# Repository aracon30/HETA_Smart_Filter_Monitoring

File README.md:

# HETA Smart Filter Monitoring &nbsp;

Industrielles Filterüberwachungssystem für den **Raspberry Pi** (3B+ / 4 / 5). Erfasst 4–20-mA-Sensordaten
via AnoPi Shield (I2C/INA219), berechnet den Filterzustand in Echtzeit und stellt bereit:

- **Weboberfläche** (lokal, kein Internet erforderlich) mit Live-Ratendiagrammen (Δp mbar/s, ΔQ, ΔT, ΔR_eff über Zyklusfortschritt) und Reststandzeit
- **OLED-Display** (Waveshare 2.42") mit Encoder-Navigation für den direkten Einsatz am Gerät
- **MQTT-Interface** für die optionale Anbindung an Cloud-Systeme und IoT-Broker
- **Modbus-TCP-Server** für die direkte Anbindung an SPS / SCADA-Leitsysteme (11 Holding-Register)
- **Lernprofil** – nach 3 Filterzyklen sekundengenaue Reststandzeit-Prognose

**Betriebsmodi:**

| Modus | Beschreibung |
|-------|-------------|
| Hardware (Standard) | Echte Sensormessung via 4–20 mA / AnoPi Shield |
| Simulation | Simulierter Filterkreislauf – ausschließlich für Tests und Präsentationen |

Kein automatischer Simulations-Fallback. Ein Sensorausfall stoppt die Messung sofort und
fordert den Bediener zur Prüfung auf.

---

## Hardware

| Komponente              | Funktion                                            |
|-------------------------|-----------------------------------------------------|
| Raspberry Pi 3B+ / 4 / 5 | Zentrale Recheneinheit                            |
| AnoPi Raspberry Shield  | 4 × 4–20 mA Analogeingänge (I2C, INA219)            |
| ifm PL5423 (×2)         | Eintrittsdruck p1 und Austrittsdruck p2 (0–10 bar)  |
| ifm TA2405              | Temperaturmessung (−50–150 °C)                      |
| Keyence FD-X            | Durchflussmessung Q (0–150 l/min, konfigurierbar)   |
| Waveshare 2.42" OLED    | Lokale Anzeige (SSD1309, SPI, 128 × 64 px)          |
| Adafruit ANO Encoder    | Menünavigation (direktes GPIO, kein I2C)             |
| 24 V Netzteil           | Sensorversorgung                                    |
| 24 V → 5 V DC/DC-Wandler| Versorgung Raspberry Pi                             |

Vollständige Pinbelegungen, Skalierungsformeln und Anschlussdiagramme:
[`docs/hardware_mapping.md`](docs/hardware_mapping.md)

**Eigene Aufsteckplatine (Entwurf):** Ein KiCad-Projekt für eine Raspberry-Pi-HAT-Platine, die
AnoPi-Shield, DC/DC-Wandler und Verdrahtung ersetzt, liegt unter
[`hardware/heta-hat/`](hardware/heta-hat/README.md) (Schaltplan fertig, Routing offen).

---

## Installation

**Voraussetzungen:** Raspberry Pi 3B+ / 4 / 5, Raspberry Pi OS Lite (Bookworm), git installiert

```bash
sudo apt install -y git
git clone https://github.com/aracon30/HETA_Smart_Filter_Monitoring.git
cd HETA_Smart_Filter_Monitoring
git checkout claude/heta-filter-monitoring
chmod +x scripts/install.sh && ./scripts/install.sh
sudo reboot
sudo systemctl start heta-monitor
```

Das Installationsskript aktiviert I2C automatisch und installiert alle Abhängigkeiten inklusive `python-anopi`.

Weboberfläche: `http://<IP-Adresse>:8080`  (IP ermitteln: `hostname -I`)

```bash
# Entwicklung / manueller Start
./scripts/start.sh

# Systemd
sudo systemctl enable heta-monitor    # Autostart beim Boot
sudo systemctl status heta-monitor    # Laufstatus
journalctl -u heta-monitor -f         # Live-Log
```

**Abhängigkeiten** (werden von `install.sh` installiert):

| Paket | Zweck | Installation |
|-------|-------|-------------|
| flask | Web-Backend | pip |
| luma.oled, Pillow | OLED-Display | pip |
| gpiozero ≥ 2.0 | Encoder-GPIO | pip |
| lgpio | GPIO-Backend Pi 5 | `sudo apt-get install python3-lgpio` |
| python-anopi | AnoPi Shield I2C/INA219 | pip |
| paho-mqtt 2.x | MQTT (optional) | pip |
| pymodbus 3.6 – 3.12 | Modbus TCP (optional) | pip |

---

## Ersteinrichtung (Onboarding)

Beim ersten Start erkennt die Software `onboarding_complete: false` in `config/settings.json`
und zeigt automatisch einen 8-stufigen Einrichtungsassistenten an.
Der Messzyklus startet erst nach Abschluss – eine laufende Simulation während des Onboardings
ist technisch blockiert.

| Schritt | Inhalt |
|---------|--------|
| 1 | Willkommen – Systemübersicht |
| 2 | HETA-Code & PIN (optional) – Code als reine Zahl eingeben (ohne „HETA-"-Präfix) oder überspringen |
| 3 | Betriebsart: **Hardware** (Realbetrieb) oder **Simulation** (nur Tests) |
| 4 | Betriebsweise: **Dauerbetrieb** (kontinuierlich) oder **Intervallbetrieb** (Batch) |
| 5 | Filterparameter: dp-Grenzwert, Druckabfall sauberer Filter, max. Durchfluss, Druckbereich |
| 6 | Temperatursensorbereich (Minimum und Maximum in °C) |
| 7 | Zugriffspasswort festlegen (mind. 4 Zeichen) |
| 8 | Zusammenfassung – Bestätigen startet das System |

> **Hinweis:** Nach Abschluss der Einrichtung wartet das System, bis ein **stabiler Durchfluss**
> erkannt wird, bevor der erste Messzyklus startet. Ein bernsteinfarbenes Overlay im Dashboard
> zeigt diesen Wartezustand an und verschwindet automatisch, sobald der Durchfluss erkannt wurde.

> **Passwort vergessen?**
> ```bash
> nano config/settings.local.json
> # settings_password_hash auf "" setzen, dann:
> sudo systemctl restart heta-monitor
> # → Onboarding startet neu
> ```

---

## HETA-Code und Prognose

### HETA-Code aktivieren

1. Weboberfläche öffnen: `http://<IP>:8080`
2. HETA-Code eingeben, z. B. `HETA-12345`
3. Zugehörigen PIN eingeben (erhältlich bei HETA bzw. über den HETA-PIN-Generator)
4. „Aktivieren" klicken

Beispiel: `HETA-12345` → PIN `486082`

### Prognosemodi

Das System passt die Reststandzeit-Anzeige automatisch an das verfügbare Wissen an:

| Modus | Bedingung | Anzeigebeispiel |
|-------|-----------|----------------|
| **BASIS** | Kein HETA-Code aktiv | `2–4 Std.` |
| **HETA-Lernend** | HETA aktiv, < 3 bestätigte Zyklen | `4–6 Std. (1/3 Zyklen)` |
| **HETA-Validiert** | HETA aktiv, ≥ 3 vollständige Zyklen | `1 Std. 52 min 30 s` |

Nach 3 Lernzyklen berechnet das System ein Referenzprofil für die nicht-lineare
dp-Kurve. Die Reststandzeit-Inversion über dieses Profil liefert eine
präzise lineare Anzeige – auch wenn der Differenzdruck exponentiell steigt.
Bei **reduzierter Schmutzfracht** (dp steigt langsamer als normal) erkennt die
Kurveninvertierung den niedrigen Fortschritt und verlängert die angezeigte Restzeit
automatisch – ohne manuelle Eingriffe.

### Lernphasen-Reset

Folgende Einstellungsänderungen löschen alle Lerndaten (3 neue Zyklen erforderlich):
`dp_limit_bar`, `flow_max_l_min`, `pressure_range_bar`, `temperature_min_c`, `temperature_max_c`

---

## Konfiguration

### Drei-Schicht-System

| Priorität | Datei | Beschreibung |
|-----------|-------|-------------|
| 1 (niedrigste) | Code-Defaults | Fallback-Werte in `config.py` |
| 2 | `config/settings.json` | Git-versionierte Standardwerte |
| 3 (höchste) | `config/settings.local.json` | Lokale Übersteuerungen, **gitignored** |

Alle Änderungen über das Dashboard oder Onboarding werden in `settings.local.json`
gespeichert. `git pull` überschreibt diese Datei nie.

### Wichtige Parameter

| Parameter | Standard | Lernrelevant ⚠ | Beschreibung |
|-----------|---------|:--------------:|-------------|
| `dp_limit_bar` | `2.5` | ✓ | Differenzdruck-Grenzwert für Filterwechsel |
| `dp_clean_bar` | `0.2` | | dp-Wert eines fabrikneuen Filters |
| `flow_max_l_min` | `150` | ✓ | Sensor-Endwert Durchfluss (= 20 mA) |
| `pressure_range_bar` | `10` | ✓ | Sensor-Endwert Drucksensoren (= 20 mA) |
| `temperature_min_c` | `-50` | ✓ | Sensor-Anfangswert Temperatur (= 4 mA) |
| `temperature_max_c` | `150` | ✓ | Sensor-Endwert Temperatur (= 20 mA) |
| `operation_mode` | `"continuous"` | | Betriebsweise: `continuous` oder `batch` |
| `flow_start_threshold_l_min` | `null` | | Manueller Durchflussschwellwert (null = automatisch) |
| `flow_stability_seconds` | `null` | | Stabilitätsfenster in Sekunden (null = auto = 10 s) |
| `flow_pause_tolerance_seconds` | `null` | | Pausentoleranz in Sekunden (null = auto: 30 s continuous / 60 s batch) |
| `flow_max_pause_days` | `7` | | Maximale Pausendauer bevor Zyklus abgebrochen wird |
| `simulation_mode` | `true` | | Simulationsmodus aktiv |
| `sampling_interval_seconds` | `1` | | Messintervall in Sekunden |
| `required_cycles_for_profile` | `3` | | Zyklen bis valides Profil |
| `webserver_port` | `8080` | | HTTP-Port der Weboberfläche |
| `mqtt_enabled` | `false` | | MQTT-Client aktivieren |
| `modbus_enabled` | `false` | | Modbus-TCP-Server aktivieren |
| `modbus_host` | `"0.0.0.0"` | | Bind-Adresse des Modbus-Servers |
| `modbus_port` | `502` | | TCP-Port (Port < 1024 benötigt Root / authbind) |
| `display_enabled` | `true` | | OLED-Display aktivieren |
| `navigation_enabled` | `true` | | Encoder-Navigation aktivieren |

⚠ Änderung löscht alle Lernzyklen und Profile.

Vollständige Parameterliste: [`docs/software_architecture.md`](docs/software_architecture.md)

---

## Software-Update

### Auf dem Raspberry Pi (empfohlen)

```bash
./scripts/update.sh
```

### Via Dashboard

Einstellungen (⚙) → „Software-Update" → „Update von GitHub holen"

Erfordert Einstellungspasswort. Das System lädt die Seite nach dem Update automatisch neu.

### Vom Entwicklungsrechner per SSH

```bash
./scripts/deploy.sh pi@192.168.1.42
```

---

## Projektstruktur

```
HETA_Smart_Filter_Monitoring/
├── backend/
│   ├── app.py              Flask-Server, REST-API, Messzyklus-Thread, Auth
│   ├── config.py           Konfigurationsmanagement (3-Schicht), Passwort-Hashing (scrypt)
│   ├── login_guard.py      Login-Bremse gegen Passwort-Raten
│   ├── sensors.py          Sensorlesemodul (SPI-ADC) + FilterSimulator
│   ├── calculations.py     dp, r_eff, Beladungsgrad, Statuslogik
│   ├── heta_code.py        HETA-Code-Validierung + PIN-Algorithmus
│   ├── learning.py         Lernzyklen + zeitbasierte Referenzprofile
│   ├── prediction.py       Reststandzeit-Prognose (3 Modi, Referenzkurven-Inversion)
│   ├── service_logic.py    Serviceempfehlungen + Berichte
│   ├── database.py         SQLite-Datenbankmodul
│   ├── display.py          OLED-Steuerung (luma.oled, PIL, 6 Bildschirme)
│   ├── navigation.py       ANO-Encoder-Navigation (gpiozero)
│   ├── mqtt_client.py      Optionaler MQTT-Client (paho-mqtt)
│   └── modbus_server.py    Optionaler Modbus-TCP-Server (pymodbus)
├── frontend/
│   ├── index.html          Dashboard, Onboarding, Einstellungs-Modal
│   ├── style.css           HETA-Industriedesign (dunkles Theme)
│   └── app.js              REST-Polling, Chart.js 4.x, Onboarding-Automat, Auth
├── config/
│   ├── settings.json       Git-versionierte Standardkonfiguration
│   └── settings.local.json Lokale Übersteuerungen (gitignored, auto-erstellt)
├── data/                   SQLite-Datenbank (gitignored, auto-erstellt)
├── logs/                   Log-Dateien (gitignored, auto-erstellt)
├── exports/                CSV-Exporte (gitignored, auto-erstellt)
├── hardware/
│   └── heta-hat/           KiCad-Projekt eigene HAT-Platine (Entwurf, siehe README dort)
├── docs/
│   ├── benutzerhandbuch.md Bedienungsanleitung für Endbenutzer
│   │                       (auch erreichbar über den ?-Button im Header der Weboberfläche)
│   ├── software_architecture.md  API, Datenbankschema, Algorithmen
│   └── hardware_mapping.md       Pinbelegungen, Skalierungsformeln
├── tests/                  pytest-Tests (Passwort-Hashing, Login-Bremse) – Aufruf: pytest -q
└── scripts/
    ├── install.sh          Erstinstallation (einmalig ausführen)
    ├── start.sh            Manueller Start ohne systemd
    ├── update.sh           Update auf dem Pi (git pull + Neustart)
    └── deploy.sh           SSH-Deploy vom Entwicklungsrechner
```

---

## REST-API

Alle Endpunkte antworten mit JSON. Geschützte Endpunkte erfordern den Header
`X-Auth-Token` (wird nach Login via `POST /api/settings/login` zurückgegeben; Token in
der URL wird nicht akzeptiert). In der Weboberfläche erscheint bei geschützten Aktionen
automatisch ein Anmeldedialog.

Schreibende Anfragen von fremden Webseiten (abweichender `Origin`-Header) werden mit
HTTP 403 abgewiesen (CSRF-Schutz).

### Öffentliche Endpunkte

| Methode | Endpunkt | Beschreibung |
|---------|----------|-------------|
| GET | `/api/status` | Vollständiger Systemstatus (wird im 1-s-Takt gepollt) |
| GET | `/api/measurements/latest` | Letzte N Messwerte (`?limit=100`) |
| GET | `/api/measurements/history` | Messwerte seit Zeitstempel (`?since=<unix>`) |
| GET | `/api/cycles` | Filterzyklen für aktiven HETA-Code |
| GET | `/api/profile` | Lernprofil + Referenzkurve (`?heta_code=`) |
| POST | `/api/heta/activate` | HETA-Code + PIN aktivieren (nur während des Onboardings ohne Login) |
| POST | `/api/sensor/recheck` | Sensoren nach Fehler erneut prüfen |
| GET | `/api/export/csv/download` | Messdaten als CSV herunterladen |
| GET | `/api/diagnostics` | Hardware-Selbstcheck |
| GET | `/help` | Benutzerhandbuch als HTML (in-app Dokumentation) |

### Authentifizierte Endpunkte (`X-Auth-Token` erforderlich)

| Methode | Endpunkt | Beschreibung |
|---------|----------|-------------|
| POST | `/api/settings/login` | Anmelden, Token erhalten |
| POST | `/api/settings/logout` | Abmelden |
| POST | `/api/settings` | Konfiguration speichern |
| POST | `/api/heta/activate` | HETA-Code + PIN aktivieren (nach dem Onboarding) |
| POST | `/api/heta/deactivate` | HETA-Code deaktivieren |
| POST | `/api/filter/confirm-change` | Filterwechsel bestätigen |
| POST | `/api/simulation/start` | Messung starten (auch: sensor_fault löschen) |
| POST | `/api/simulation/stop` | Messung stoppen |
| POST | `/api/simulation/reset` | System zurücksetzen |
| POST | `/api/simulation/quick-learn` | Lernzyklen simulieren |
| POST | `/api/simulation/set-rates` | Simulations-Szenario setzen |
| POST | `/api/navigation/event` | Encoder-Ereignis simulieren |
| POST | `/api/update/pull` | git pull + Neustart |

Vollständige API-Dokumentation mit Feldbeschreibungen:
[`docs/software_architecture.md`](docs/software_architecture.md)

---

## Fehlersuche

### Software startet nicht

```bash
source .venv/bin/activate && python3 backend/app.py   # Fehler direkt sehen
journalctl -u heta-monitor -n 50 --no-pager           # systemd-Logs
```

### Weboberfläche nicht erreichbar

```bash
hostname -I                           # IP-Adresse des Pi ermitteln
sudo systemctl status heta-monitor   # Läuft der Dienst?
ss -tlnp | grep 8080                  # Port belegt durch anderen Prozess?
```

### Sensoren werden nicht erkannt (alle 4 Kanäle KABELBRUCH)

- I2C aktiviert? `ls /dev/i2c-*` muss mindestens `/dev/i2c-1` zeigen
- Falls nicht: `sudo raspi-config` → Interface Options → I2C → Yes → Neustart
- GND des 24V-Netzteils mit GND des Raspberry Pi verbinden (gemeinsame Masse)
- Test: `python3 -c "from python_anopi import AnoPi; a=AnoPi(); print(a.ai_mA(0))"`

### OLED-Display zeigt nichts

- SPI aktiviert? `ls /dev/spidev*` muss `/dev/spidev0.0` zeigen
- DC-Pin → GPIO 25 (Board-Pin 22), RES-Pin → GPIO 27 (Board-Pin 13)
- Vollständige Belegung: [`docs/hardware_mapping.md`](docs/hardware_mapping.md)
- Display deaktiviert? `display_enabled: true` in `config/settings.local.json` prüfen

### Encoder reagiert nicht

- COMA und COMB müssen an **GND** angeschlossen sein (nicht VCC)
- `pip install gpiozero lgpio` oder `sudo apt-get install python3-lgpio`
- GPIO-Pins in `config/settings.json` prüfen (`encoder_pin_enca` etc.)

### Sensor-Fault (rotes Overlay im Browser)

1. Verdrahtung und Sensorversorgung der genannten Kanäle prüfen
2. „Alle Sensoren angeschlossen – System prüfen" klicken
3. Für Testbetrieb ohne Hardware: Simulationsmodus im Overlay aktivieren (Passwort erforderlich)

### Bernsteinfarbenes Overlay erscheint nach Start

Das System wartet auf stabilen Durchfluss, bevor der erste Messzyklus startet. Falls das Overlay
dauerhaft bleibt: Pumpe prüfen, Durchfluss sicherstellen oder den manuellen Durchflussschwellwert
in den Einstellungen (Betriebsweise & Durchflusserkennung) senken.

### „Zu viele Fehlversuche“ beim Anmelden

Nach 5 falschen Passwörtern sperrt das System die Anmeldung von dieser Adresse für 30 s;
jeder weitere Fehlversuch verdoppelt die Sperre (max. 15 min). Abwarten oder den Dienst
neu starten (`sudo systemctl restart heta-monitor`) hebt die Sperre auf.

### Passwort vergessen

```bash
nano config/settings.local.json
# Zeile "settings_password_hash" auf "" setzen
sudo systemctl restart heta-monitor
# → Onboarding-Assistent startet neu, neues Passwort festlegen
```

### Lerndaten ungewollt zurückgesetzt

Erwartetes Verhalten: Änderung eines lernrelevanten Parameters (`dp_limit_bar`,
`flow_max_l_min`, `pressure_range_bar`, `temperature_min_c`, `temperature_max_c`) löscht automatisch alle
Zyklen und Profile. Das System muss erneut 3 Filterzyklen durchlaufen.

### Onboarding erscheint nach jedem Start

```bash
grep onboarding_complete config/settings.local.json   # Muss "true" sein
# Falls Datei fehlt oder Wert false: Onboarding erneut abschließen
```

---

## Endbenutzer-Anleitung

Für die Bedienung der Weboberfläche (Dashboard, HETA-Code, Filterwechsel, OLED-Display):
[`docs/benutzerhandbuch.md`](docs/benutzerhandbuch.md)

Das Benutzerhandbuch ist auch direkt in der Weboberfläche über den **`?`-Button** im Header
erreichbar – ohne separaten Download oder Dateiöffnung.

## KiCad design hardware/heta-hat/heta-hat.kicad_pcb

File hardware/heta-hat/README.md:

# HETA-HAT – eigene Aufsteckplatine für den Raspberry Pi (Entwurf v0.1)

KiCad-Projekt einer Raspberry-Pi-HAT-Platine (65 × 56,5 mm), die den heutigen Modulaufbau
ersetzt: **AnoPi-Shield, externer 24-V→5-V-Wandler und die fliegende Verdrahtung** von OLED
und Encoder wandern auf eine Platine.

> **Status: Entwurf, nicht fertigungsreif.** Schaltplan und Bauteilplatzierung sind fertig und
> geprüft, **die Leiterbahnen sind noch nicht geroutet** (offene Punkte siehe unten).
> Werte mit `*` vor der Fertigung gegen das Datenblatt prüfen.

| Schaltplan | Platzierung (Oberseite) |
|---|---|
|  |  |

Schaltplan als PDF: [`fertigung/heta-hat-schaltplan.pdf`](fertigung/heta-hat-schaltplan.pdf) ·
Stückliste: [`fertigung/heta-hat-stueckliste.csv`](fertigung/heta-hat-stueckliste.csv)

---

## Funktionsblöcke

| Block | Lösung |
|---|---|
| 24-V-Eingang | PTC-Sicherung 1,5 A (F1), Verpolschutz-Schottky SS34 (D1), TVS SMBJ28A (D2), 47 µF gegen Kabelresonanz |
| 5-V-Versorgung Pi | Schaltregler TI LMR33630A (400 kHz, 3 A), speist den Pi über GPIO-Pin 2/4, EN-Schwelle ≈ 8 V, Betriebs-LED |
| 4 × 4–20 mA | Je Kanal: abgesicherte Sensorversorgung (PTC 100 mA), PTC 50 mA vor der Bürde, TVS SMAJ12A, Bürde 120 Ω 0,1 %, RC-Tiefpass 1 kΩ/100 nF, Klemmdioden BAT54S auf 0…3,3 V |
| ADC | TI ADS1115, 16 Bit, I²C-Adresse **0x48**, ALERT/RDY an GPIO 6 |
| HAT-ID-EEPROM | 24LC32 an ID_SD/ID_SC (Adresse 0x50), Schreibschutz per Lötbrücke JP1 lösbar |
| OLED / Encoder | JST-PH-Stecker (verriegelnd), **gleiche GPIO-Belegung wie heute** – `config/settings.json` bleibt unverändert |

### Auslegung 4–20 mA

- Bürde 120 Ω: 4 mA = 0,48 V · 20 mA = 2,40 V · 25 mA = 3,00 V (Reserve für NAMUR-NE43-Fehlerströme bis 21 mA und darüber)
- ADS1115 im Bereich ±4,096 V: 125 µV/LSB ≙ **1,04 µA** Auflösung (≈ 0,007 % der 16-mA-Spanne)
- Für 2-Leiter-Sensoren bleiben bei 24 V und 20 mA rund 20 V Schleifenspannung
- Fehlanschluss von 24 V direkt auf den Signaleingang: PTC F3/F5/F7/F9 löst aus, TVS und Klemmdioden schützen den ADC

### Steckerbelegung

| Stecker | Pin | Signal |
|---|---|---|
| **J1** 24 V DC (Phoenix MC 1,5/2-G-3,5, linke Kante) | 1 / 2 | +24 V / GND |
| **J2** Sensoren (Phoenix MC 1,5/12-G-3,5, Unterkante, für 4 × 3-pol. Stecker) | 1–3 | CH1 p1: +24 V (abgesichert), Signal, GND |
| | 4–6 | CH2 p2: +24 V, Signal, GND |
| | 7–9 | CH3 T: +24 V, Signal, GND |
| | 10–12 | CH4 Q: +24 V, Signal, GND |
| **J6** OLED (JST PH 7-pol.) | 1–7 | 3V3, GND, DIN (GPIO 10), CLK (GPIO 11), CS (GPIO 8), DC (GPIO 25), RES (GPIO 24) |
| **J7** Encoder (JST PH 9-pol.) | 1–9 | COMA=GND, ENCA (16), ENCB (20), SW1 (21), COMB=GND, SW2 (12), SW3 (13), SW4 (19), SW5 (26) |
| **J8** GPIO (2 × 20 Buchse, Unterseite) | | I²C1 (GPIO 2/3) für den ADC, ID_SD/ID_SC (GPIO 0/1) für das EEPROM |

2-Leiter-Sensoren (ifm PL5423, TA2405) zwischen „+24 V“ und „Signal“, 3/4-Leiter-Sensoren
(Keyence FD-X) mit eigener Versorgung zwischen „Signal“ und „GND“.

---

## Offene Punkte vor der Fertigung

- [ ] **Routing.** Den Leistungsteil (U1, C2–C4, L1, C7–C10) nach dem Layoutbeispiel im
      LMR33630-Datenblatt führen: kurze Schleife VIN–Cin–GND, kleine SW-Fläche, FB-Leitung weg
      von SW. Analogeingänge getrennt vom Schaltregler, GND-Flächen auf beiden Lagen sind angelegt.
      Netzklassen sind vorbereitet (Power 0,8 mm, 24 V Sensorversorgung 0,5 mm, Signal 0,25 mm).
- [ ] **Werte mit `*` prüfen:** PTC-Typen (Haltestrom, Spannungsfestigkeit ≥ 30 V), Spule
      (≥ 4 A Sättigungsstrom), Stromverbrauch des Keyence FD-X gegen PTC 100 mA.
- [ ] **Rückspeiseschutz:** Die 5 V gehen direkt auf den GPIO-Header. Solange keine ideale Diode
      ergänzt ist, **nie gleichzeitig ein USB-C-Netzteil am Pi und 24 V an J1** anschließen.
- [ ] **Raspberry Pi 5:** 3 A reichen für Pi 5 mit Display und Encoder. Ohne USB-PD-Netzteil
      begrenzt der Pi 5 die USB-Ports auf 600 mA; für mehr USB-Last wäre ein 5-A-Regler nötig.
- [ ] **EMV:** Bei langen Sensorleitungen ggf. Gleichtaktdrossel/Ferrite an J1 und J2, Schirm
      auf PE am Gehäuse. Für die CE-Kennzeichnung ist eine EMV-Prüfung nötig.
- [ ] **Software:** `backend/sensors.py` liest heute das AnoPi-Shield (`python-anopi`). Für die
      HAT-Platine wird ein ADS1115-Treiber gebraucht (I²C 0x48, Messwert / 120 Ω = Strom).
- [ ] **HAT-EEPROM** nach der Bestückung mit `eepmake`/`eepflash` (Raspberry-Pi-Tools)
      beschreiben; dazu JP1 schließen.

---

## Arbeiten mit dem Projekt

- Öffnen mit **KiCad 7 oder neuer** (`heta-hat.kicad_pro`). KiCad 8/9 konvertieren die Dateien
  beim ersten Speichern; Symbole und Footprints stammen aus den Standardbibliotheken.
- Exporte (Schaltplan-PDF, Stückliste, Gerber, Bohr- und Bestückdaten):

  ```bash
  ./hardware/heta-hat/scripts/export.sh
  ```

  Gerber- und Bestückdaten werden nicht versioniert (`.gitignore`), weil sie erst nach dem
  Routing gültig sind.

### Was bereits geprüft ist

- **Verdrahtung:** Die aus dem Schaltplan exportierte Netzliste wurde automatisch gegen die
  Sollverdrahtung abgeglichen (46 Netze, alle Pins korrekt, keine Netze mit nur einem Anschluss).
- **DRC:** keine Bauteilüberlappungen, keine Abstands- oder Kantenfehler. Offen sind nur die
  99 noch nicht gerouteten Verbindungen und zwei Thermal-Hinweise an GND-Pads, die sich beim
  Routen erledigen. Silkscreen-Hinweise (überlappende Referenzen) sind kosmetisch.
- **Mechanik:** Kontur, Radien und Montagelöcher (M2,5 bei 3,5 / 61,5 × 3,5 / 52,5 mm) sowie
  die Lage der GPIO-Leiste (Pin 1 bei 8,37 / 4,77 mm) nach Raspberry-Pi-HAT-Spezifikation.

Die Dateien wurden mit KiCad 7.0.11 erzeugt (Schaltplan und Platzierung skriptgesteuert,
danach regulär in KiCad weiterbearbeitbar).

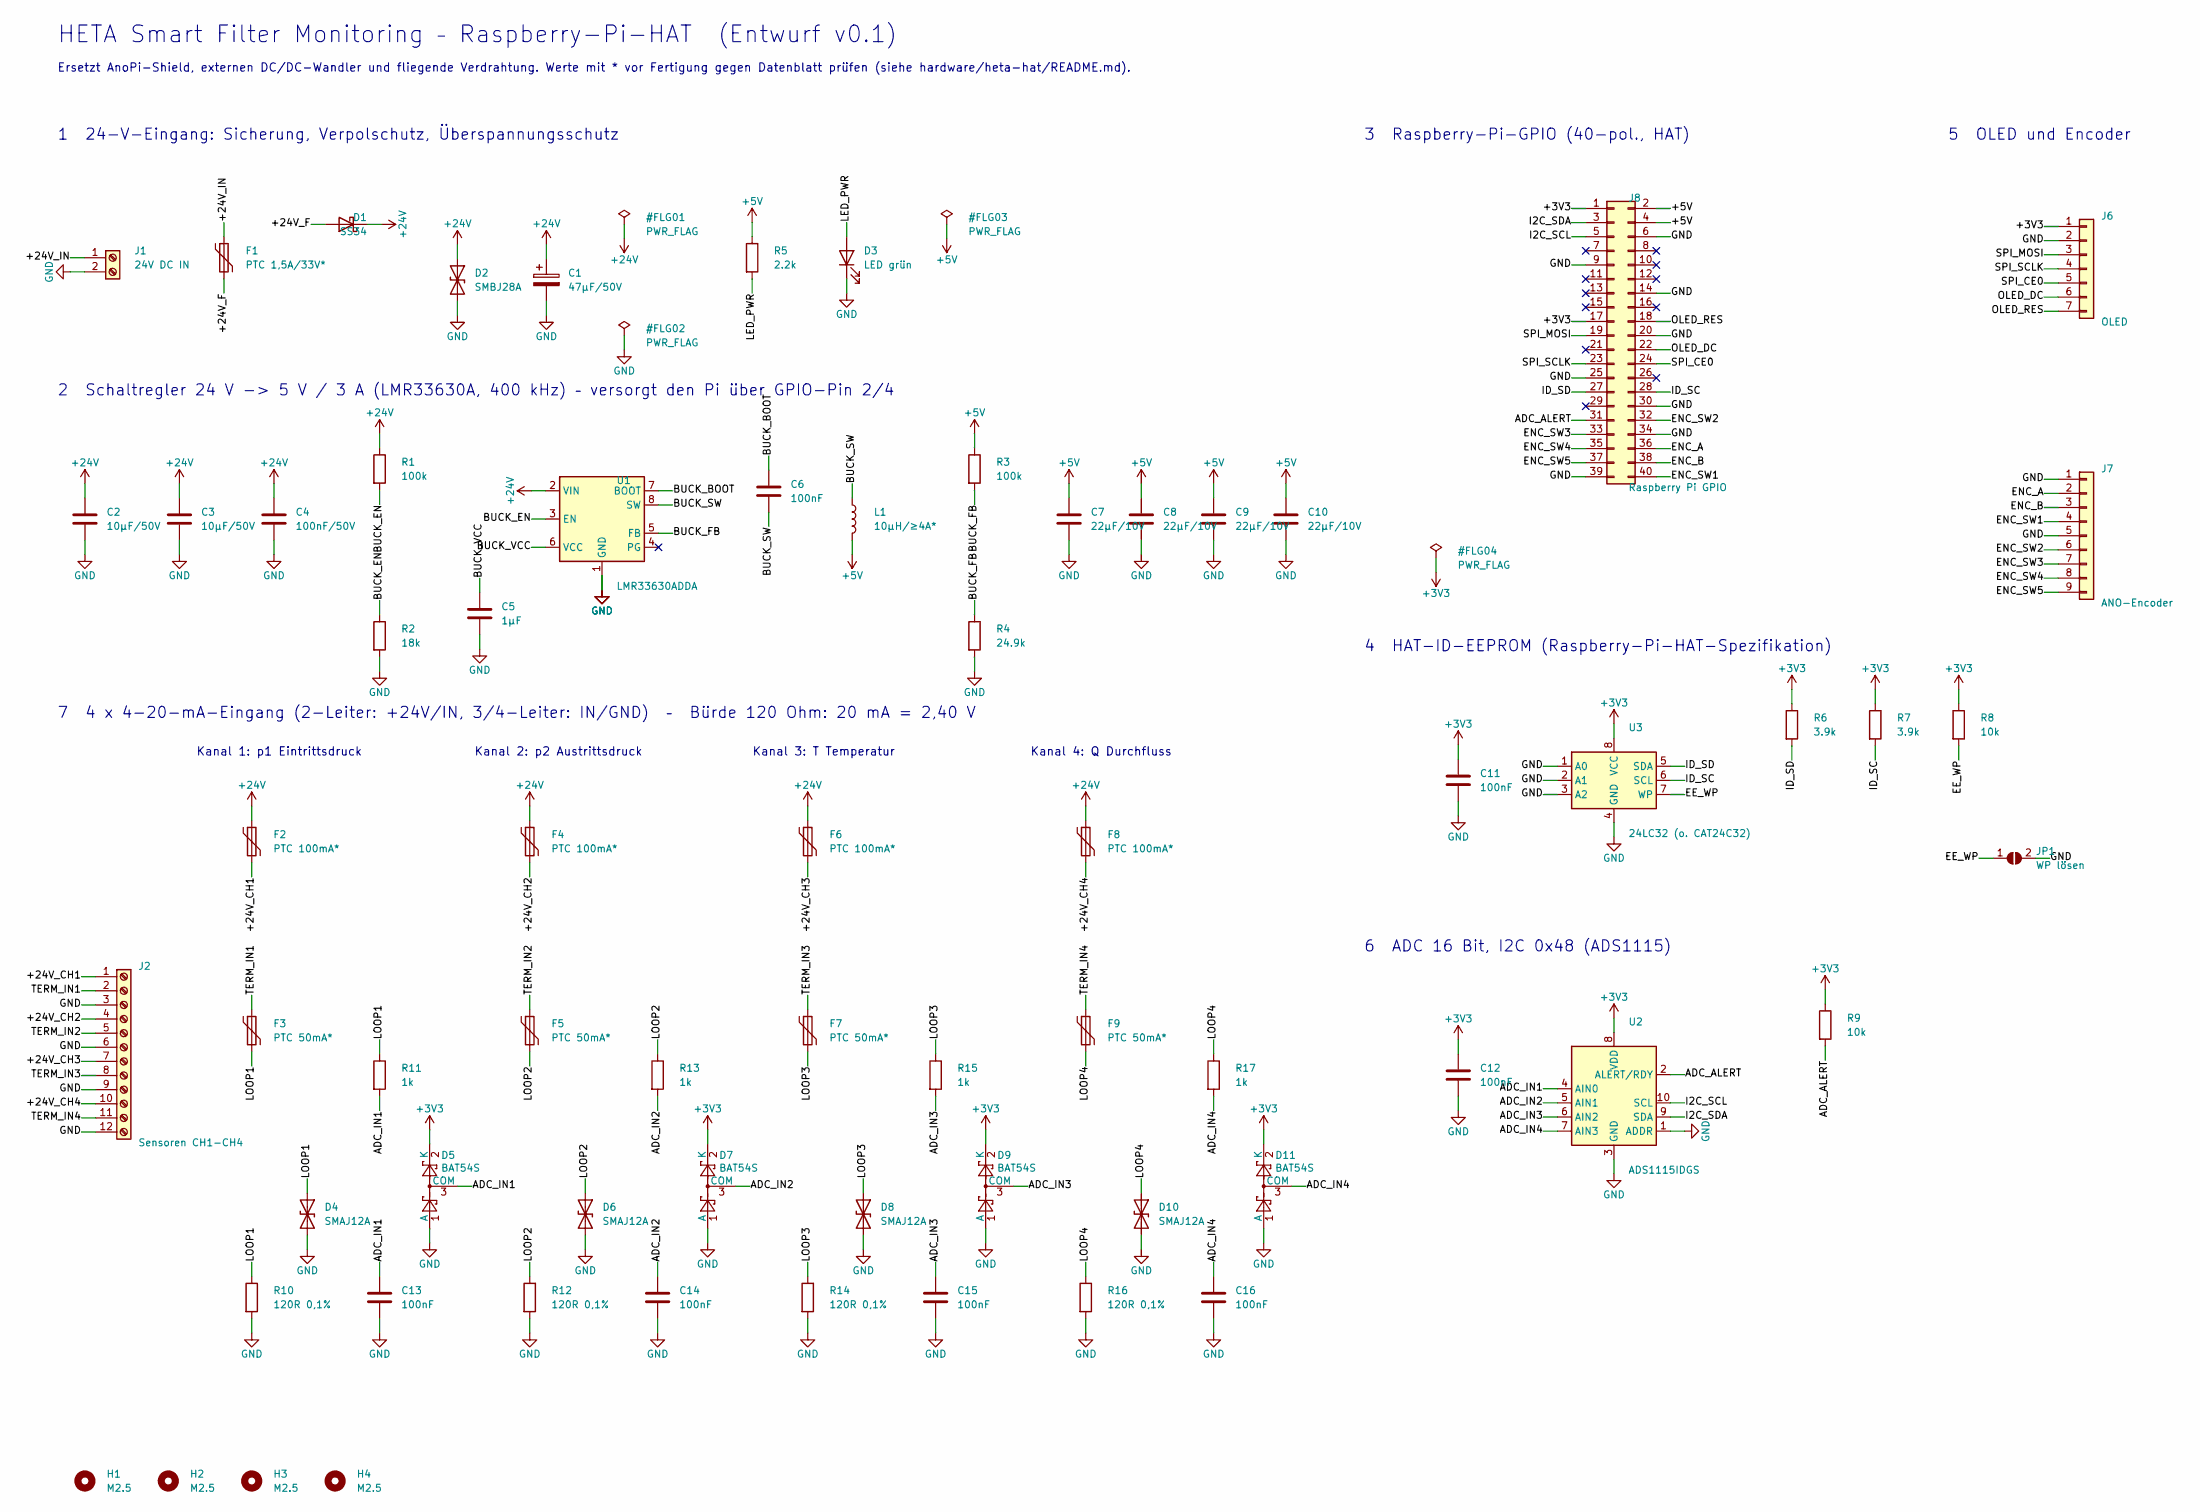
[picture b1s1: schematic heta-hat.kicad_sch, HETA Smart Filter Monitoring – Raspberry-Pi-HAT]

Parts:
C1: 47µF/50V; CP_Elec_6.3x7.7
C2, C3: 10µF/50V; C_1210_3225Metric
C4: 100nF/50V; C_0603_1608Metric
C5: 1µF; C_0603_1608Metric
C6, C11, C12, C13, C14, C15, C16: 100nF; C_0603_1608Metric
C7, C8, C9, C10: 22µF/10V; C_1206_3216Metric
D1: SS34; D_SMA
D2: SMBJ28A; D_SMB
D3: LED grün; LED_0603_1608Metric
D4, D6, D8, D10: SMAJ12A; D_SMA
D5, D7, D9, D11: BAT54S; SOT-23
F1: PTC 1,5A/33V*; Fuse_1812_4532Metric; MPN Bourns MF-MSMF150/33X (o. glw.)
F2, F4, F6, F8: PTC 100mA*; Fuse_1206_3216Metric
F3, F5, F7, F9: PTC 50mA*; Fuse_1206_3216Metric
H1, H2, H3, H4: M2.5; MountingHole_2.7mm_M2.5
J1: 24V DC IN; PhoenixContact_MC_1,5_2-G-3.5_1x02_P3.50mm_Horizontal; MPN Phoenix MC 1,5/2-G-3,5 + Stecker MC 1,5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
J2: Sensoren CH1-CH4; PhoenixContact_MC_1,5_12-G-3.5_1x12_P3.50mm_Horizontal; MPN Phoenix MC 1,5/12-G-3,5 + 4 x Stecker M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
J6: OLED; JST_PH_B7B-PH-K_1x07_P2.00mm_Vertical
J7: ANO-Encoder; JST_PH_B9B-PH-K_1x09_P2.00mm_Vertical
J8: Raspberry Pi GPIO; PinSocket_2x20_P2.54mm_Vertical; MPN 2x20 Buchsenleiste 2,54 mm (Stacking od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
JP1: WP lösen; SolderJumper-2_P1.3mm_Open_RoundedPad1.0x1.5mm
L1: 10µH/≥4A*; L_Bourns_SRP7028A_7.3x6.6mm; MPN Bourns SRP7028A-100M
R1, R3: 100k; R_0603_1608Metric
R2: 18k; R_0603_1608Metric
R4: 24.9k; R_0603_1608Metric
R5: 2.2k; R_0603_1608Metric
R6, R7: 3.9k; R_0603_1608Metric
R8, R9: 10k; R_0603_1608Metric
R10, R12, R14, R16: 120R 0,1%; R_1206_3216Metric
R11, R13, R15, R17: 1k; R_0603_1608Metric
U1: LMR33630ADDA; Texas_HSOP-8-1EP_3.9x4.9mm_P1.27mm_ThermalVias
U2: ADS1115IDGS; TSSOP-10_3x3mm_P0.5mm
U3: 24LC32 (o. CAT24C32); SOIC-8_3.9x4.9mm_P1.27mm

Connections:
+3V3: C11.1, C12.1, D5.2 (K), D7.2 (K), D9.2 (K), D11.2 (K), J6.1, J8.1, J8.17, R6.1, R7.1, R8.1, R9.1, U2.8 (VDD), U3.8 (VCC)
+5V: C7.1, C8.1, C9.1, C10.1, J8.2, J8.4, L1.2, R3.1, R5.1
+24V: C1.1, C2.1, C3.1, C4.1, D1.1 (K), D2.1 (A1), F2.1, F4.1, F6.1, F8.1, R1.1, U1.2 (VIN)
+24V_CH1: F2.2, J2.1
+24V_CH2: F4.2, J2.4
+24V_CH3: F6.2, J2.7
+24V_CH4: F8.2, J2.10
+24V_F: D1.2 (A), F1.2
+24V_IN: F1.1, J1.1
ADC_ALERT: J8.31, R9.2, U2.2 (ALERT/RDY)
ADC_IN1: C13.1, D5.3 (COM), R11.2, U2.4 (AIN0)
ADC_IN2: C14.1, D7.3 (COM), R13.2, U2.5 (AIN1)
ADC_IN3: C15.1, D9.3 (COM), R15.2, U2.6 (AIN2)
ADC_IN4: C16.1, D11.3 (COM), R17.2, U2.7 (AIN3)
BUCK_BOOT: C6.1, U1.7 (BOOT)
BUCK_EN: R1.2, R2.1, U1.3 (EN)
BUCK_FB: R3.2, R4.1, U1.5 (FB)
BUCK_SW: C6.2, L1.1, U1.8 (SW)
BUCK_VCC: C5.1, U1.6 (VCC)
EE_WP: JP1.1 (A), R8.2, U3.7 (WP)
ENC_A: J7.2, J8.36
ENC_B: J7.3, J8.38
ENC_SW1: J7.4, J8.40
ENC_SW2: J7.6, J8.32
ENC_SW3: J7.7, J8.33
ENC_SW4: J7.8, J8.35
ENC_SW5: J7.9, J8.37
GND: C1.2, C2.2, C3.2, C4.2, C5.2, C7.2, C8.2, C9.2, C10.2, C11.2, C12.2, C13.2, C14.2, C15.2, C16.2, D2.2 (A2), D3.1 (K), D4.2 (A2), D5.1 (A), D6.2 (A2), D7.1 (A), D8.2 (A2), D9.1 (A), D10.2 (A2), D11.1 (A), J1.2, J2.3, J2.6, J2.9, J2.12, J6.2, J7.1, J7.5, J8.6, J8.9, J8.14, J8.20, J8.25, J8.30, J8.34, J8.39, JP1.2 (B), R2.2, R4.2, R10.2, R12.2, R14.2, R16.2, U1.1 (GND), U1.9 (GND), U2.1 (ADDR), U2.3 (GND), U3.1 (A0), U3.2 (A1), U3.3 (A2), U3.4 (GND)
I2C_SCL: J8.5, U2.10 (SCL)
I2C_SDA: J8.3, U2.9 (SDA)
ID_SC: J8.28, R7.2, U3.6 (SCL)
ID_SD: J8.27, R6.2, U3.5 (SDA)
LED_PWR: D3.2 (A), R5.2
LOOP1: D4.1 (A1), F3.2, R10.1, R11.1
LOOP2: D6.1 (A1), F5.2, R12.1, R13.1
LOOP3: D8.1 (A1), F7.2, R14.1, R15.1
LOOP4: D10.1 (A1), F9.2, R16.1, R17.1
OLED_DC: J6.6, J8.22
OLED_RES: J6.7, J8.18
SPI_CE0: J6.5, J8.24
SPI_MOSI: J6.3, J8.19
SPI_SCLK: J6.4, J8.23
TERM_IN1: F3.1, J2.2
TERM_IN2: F5.1, J2.5
TERM_IN3: F7.1, J2.8
TERM_IN4: F9.1, J2.11

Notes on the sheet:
HETA Smart Filter Monitoring – Raspberry-Pi-HAT (Entwurf v0.1)
Ersetzt AnoPi-Shield, externen DC/DC-Wandler und fliegende Verdrahtung. Werte mit * vor Fertigung gegen Datenblatt prüfen (siehe hardware/heta-hat/README.md).
1 24-V-Eingang: Sicherung, Verpolschutz, Überspannungsschutz
2 Schaltregler 24 V -> 5 V / 3 A (LMR33630A, 400 kHz) – versorgt den Pi über GPIO-Pin 2/4
3 Raspberry-Pi-GPIO (40-pol., HAT)
4 HAT-ID-EEPROM (Raspberry-Pi-HAT-Spezifikation)
5 OLED und Encoder
6 ADC 16 Bit, I2C 0x48 (ADS1115)
7 4 x 4-20-mA-Eingang (2-Leiter: +24V/IN, 3/4-Leiter: IN/GND) – Bürde 120 Ohm: 20 mA = 2,40 V
Kanal 1: p1 Eintrittsdruck
Kanal 2: p2 Austrittsdruck
Kanal 3: T Temperatur
Kanal 4: Q Durchfluss

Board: 2 copper layers, 67 parts (1 on the bottom side), 46 nets, no tracks yet.

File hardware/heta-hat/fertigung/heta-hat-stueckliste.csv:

Pos;Menge;Referenzen;Wert;Footprint;MPN / Vorschlag;Funktion / Spezifikation
1;1;C1;47µF/50V;CP_Elec_6.3x7.7;;Dämpfung Kabelinduktivität
2;2;C2, C3;10µF/50V;C_1210_3225Metric;;
3;1;C4;100nF/50V;C_0603_1608Metric;;
4;1;C5;1µF;C_0603_1608Metric;;
5;7;C6, C11, C12, C13, C14, C15, C16;100nF;C_0603_1608Metric;;C13: Tiefpass fg ~1,6 kHz | C14: Tiefpass fg ~1,6 kHz | C15: Tiefpass fg ~1,6 kHz | C16: Tiefpass fg ~1,6 kHz
6;4;C7, C8, C9, C10;22µF/10V;C_1206_3216Metric;;
7;1;D1;SS34;D_SMA;;Verpolschutz
8;1;D2;SMBJ28A;D_SMB;;Überspannung, unidirektional, Kathode = Pin 1
9;1;D3;LED grün;LED_0603_1608Metric;;Betriebsanzeige 5 V
10;4;D4, D6, D8, D10;SMAJ12A;D_SMA;;Surge/ESD, Kathode = Pin 1
11;4;D5, D7, D9, D11;BAT54S;SOT-23;;Klemmung auf 0..3,3 V
12;1;F1;PTC 1,5A/33V*;Fuse_1812_4532Metric;Bourns MF-MSMF150/33X (o. glw.);
13;4;F2, F4, F6, F8;PTC 100mA*;Fuse_1206_3216Metric;;Sensorversorgung absichern
14;4;F3, F5, F7, F9;PTC 50mA*;Fuse_1206_3216Metric;;Schutz der Bürde bei Fehlanschluss
15;1;J1;24V DC IN;PhoenixContact_MC_1,5_2-G-3.5_1x02_P3.50mm_Horizontal;Phoenix MC 1,5/2-G-3,5 + Stecker MC 1,5/2-ST-3,5;
16;1;J2;Sensoren CH1-CH4;PhoenixContact_MC_1,5_12-G-3.5_1x12_P3.50mm_Horizontal;Phoenix MC 1,5/12-G-3,5 + 4 x Stecker MC 1,5/3-ST-3,5 (anreihbar);je Kanal: +24V (abgesichert), Signal, GND – CH1 = Pin 1-3 ... CH4 = Pin 10-12
17;1;J6;OLED;JST_PH_B7B-PH-K_1x07_P2.00mm_Vertical;;VCC GND DIN CLK CS DC RES (wie Waveshare-Modul)
18;1;J7;ANO-Encoder;JST_PH_B9B-PH-K_1x09_P2.00mm_Vertical;;COMA ENCA ENCB SW1 COMB SW2 SW3 SW4 SW5
19;1;J8;Raspberry Pi GPIO;PinSocket_2x20_P2.54mm_Vertical;2x20 Buchsenleiste 2,54 mm (Stacking oder Standard);
20;1;JP1;WP lösen;SolderJumper-2_P1.3mm_Open_RoundedPad1.0x1.5mm;;Brücke schließen zum Programmieren
21;1;L1;10µH/≥4A*;L_Bourns_SRP7028A_7.3x6.6mm;Bourns SRP7028A-100M;
22;2;R1, R3;100k;R_0603_1608Metric;;R3: Vout = 1 V x (1 + 100k/24,9k) = 5,02 V
23;1;R2;18k;R_0603_1608Metric;;EN-Schwelle ~8 V
24;1;R4;24.9k;R_0603_1608Metric;;
25;1;R5;2.2k;R_0603_1608Metric;;
26;2;R6, R7;3.9k;R_0603_1608Metric;;
27;2;R8, R9;10k;R_0603_1608Metric;;R8: Schreibschutz aktiv
28;4;R10, R12, R14, R16;120R 0,1%;R_1206_3216Metric;;"Bürde 4-20 mA; 0,1 %, ≤25 ppm/K, ≥0,25 W"
29;4;R11, R13, R15, R17;1k;R_0603_1608Metric;;
30;1;U1;LMR33630ADDA;Texas_HSOP-8-1EP_3.9x4.9mm_P1.27mm_ThermalVias;;
31;1;U2;ADS1115IDGS;TSSOP-10_3x3mm_P0.5mm;;
32;1;U3;24LC32 (o. CAT24C32);SOIC-8_3.9x4.9mm_P1.27mm;;

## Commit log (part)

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2026-05-08 Initial Raspberry Pi 5 prototype software for HETA Smart Filter Monitoring
    Vollständige Prototyp-Software mit folgenden Modulen:
    - backend/sensors.py: 4-Kanal 4-20mA Sensorlesung + Filtersimulator
    - backend/calculations.py: Differenzdruck, R_eff, Filterzustand, Statuslogik
    - backend/heta_code.py: HETA-Code-Validierung + PIN-Algorithmus
    - backend/learning.py: Lernzyklen und Referenzprofile (3 Zyklen)
    - backend/prediction.py: Reststandzeit-Prognose mit exponentieller Glättung
2026-05-11 Display: korrekte GPIO-Pins für SSD1309 SPI (DC=25, RST=27) und Doku aktualisiert
    - display.py: gpio_DC=25, gpio_RST=27 als Standardwerte (Waveshare 2.42" OLED Spec)
    - I2C-Fallback ebenfalls auf ssd1309 korrigiert (vorher ssd1306)
    - hardware_mapping.md: falsche Pinbelegung (DC=GPIO24, RST=GPIO25) korrigiert
    - Komplette SPI/I2C-Pinbelegungstabellen mit Board-Pin-Nummern ergänzt
    - Bildschirmreihenfolge und Encoder-Tastenbelegung dokumentiert
    https://claude.ai/code/session_01SKNmjdNUtbmKGLrJ9zgL6h
2026-05-12 Settings: MQTT, Display und Encoder konfigurierbar gemacht
    config/settings.json + config.py (_DEFAULTS):
    - mqtt_broker, mqtt_port, mqtt_client_id ergänzt
    - display_enabled, display_use_spi, display_spi_port/device, display_gpio_dc/rst, display_i2c_address ergänzt
    - navigation_enabled, encoder_i2c_address ergänzt
    - settings.json mit Leerzeilen strukturiert (Gruppen)
    app.py:
2026-05-12 Bugfix: Port belegt nach Update behoben
    backend/app.py:
    - os.execv() als Fallback-Neustart entfernt — dieser Mechanismus vererbte den
    offenen Flask-Socket an den neuen Prozess, der dann Port 8080 nicht binden konnte
    - Ersetzt durch os._exit(0): sauberes Beenden, systemd (Restart=always) startet
    den Prozess neu ohne Socket-Vererbung
    - systemctl-Timeout erhöht: 5 s → 10 s (mehr Zeit für graceful shutdown)
2026-05-12 Simulation: vollständig rauschfrei und gleichmäßig
    Alle random.gauss()-Aufrufe und die Sinusschwingung entfernt.
    Die Kurven steigen/fallen jetzt deterministisch und ohne Sprünge:
    - dp: rein S-förmig (progress^1.5), kein Gauss, keine Sinus-Überlagerung
    - p1: konstant 3,5 bar; p2 = p1 - dp
    - flow: linearer Abfall proportional zu dp_fraction
    - temp: linearer Anstieg 20 → 35 °C
2026-05-12 docs(readme): Simulationsmodus-Hinweis präzisiert
    "Fallback" → "kein automatischer Fallback, bewusst aktivierbar"
    https://claude.ai/code/session_01SKNmjdNUtbmKGLrJ9zgL6h
2026-05-18 Add reset of learning cycles per HETA code
    - database.py: new reset_cycles_for_heta(heta_code) deletes cycles and
    profile only for the specified code (vs. reset_all which wipes everything)
    - app.py: POST /api/heta/reset-cycles (requires auth token) — aborts the
    active learning cycle, clears DB, resets predictor and analysis state,
    logs a service event
    - index.html: "Lernzyklen zurücksetzen" danger button in Zyklen & Profil tab
2026-05-18 Fix simulation bugs: r_eff_limit, health reset, cycle reset after quick-learn
    - Bug #6: Use reference_r_eff_end (actual measured end R_eff) as r_eff_limit
    instead of derived dp_limit/avg_flow; keeps old profiles working via fallback
    - Bug #1: Reset simulation step counter and _smoothed_health_pct after
    quick-learn so cycle 4 starts from step 0 with clean state
    - Bug #3: Reset _smoothed_health_pct when learning-sensitive settings change
    - Bug #11: Clamp t_pct to [0, 100] in get_curve_analysis (negative elapsed guard)
2026-05-19 fix: Reststandzeit = 0 wenn dp-Limit erreicht
    Sobald dp_bar >= dp_limit gilt, wird remaining_s auf 0.0 gezwungen
    bevor get_status() aufgerufen wird. Gilt für Sensor- und Simulationsbetrieb.
    https://claude.ai/code/session_01SKNmjdNUtbmKGLrJ9zgL6h
2026-05-19 cleanup: README kürzen, Logout-Bug beheben, Legacy-Kommentare entfernen
    - README.md von 777 auf ~215 Zeilen reduziert: klarer Schnellstart,
    Encoder-Beschreibung korrigiert (GPIO, nicht I2C/Seesaw), API-Referenz
    auf docs/ verwiesen, Fehlersuche komprimiert
    - app.py Zeile 1390 (Logout): Python-Präzedenz-Bug behoben –
    `silent=True or {}` wurde zu `(get_json(...) or {})` korrigiert,
    verhindert AttributeError wenn kein JSON-Body vorhanden
2026-05-19 Fix inconsistent Filterzustand between health tile and service message
    The health tile displayed smoothed_health (R_eff-based when profile is
    valid, plus ratchet smoothing), while the service message used
    fs.filter_health_percent — the raw, unsmoothed, dp-only value from
    calculate_filter_state(). These diverged visibly when R_eff-based
    health tracking was active.
    Fix: generate_service_recommendation() gains an optional health_percent
2026-05-20 Add custom chart toggle chips and y-axis assignment panel
    - Add DS_META and AXIS_OPTIONS constants for dataset metadata
    - Add _buildChartToggleButtons(): live chips (0-6) above chart, reference chips (dp/Q/T/R_eff groups) below chart; ref chips start disabled until data loads
    - Add _buildAxisPanel(): collapsible y-axis assignment with dropdowns for non-fixed datasets, read-only labels for yPressure datasets
    - Add toggleChartDs(), setDatasetAxis(), updateAxisVisibility(), toggleAxisPanel(), _refreshRefChips()
    - Extend updateReferenceOverlay() to populate all 19 datasets (flow/temp/reff ref+tolerance bands ds10-18) using tolerance_flow_pct, tolerance_temp_c, tolerance_reff_pct from API
    - Updat
2026-05-20 feat: R_eff als Widerstandsfaktor ×N.NN statt bar·min/l anzeigen
    Dashboard-Kachel "Filterwiderstand" zeigt jetzt:
    - Bei validem Profil: ×N.NN (dimensionslos, R_eff / R_eff_Referenzstart)
    z. B. ×1.35 = 35 % mehr Widerstand als ein frischer Referenzfilter
    - Während Lernphase (kein Profil): Fallback auf mbar·min/l (×1000,
    besser lesbare Zahlen als bar·min/l)
    Referenzkurve im Chart: r_eff-Punkte werden durch reference_r_eff_start
2026-05-20 fix: Reststandzeit durch Referenzkurven-Inversion – echte Gerade trotz nichtlinearem dp
    Methode update_with_reference_curve():
    - Invertiert die gelernte Referenzkurve: dp_bar → t_pct
    - remaining = ref_duration × (1 − t_pct/100) → immer gerade Linie
    - Nichtlinearer dp-Anstieg (clogging^1.8) wird durch Inversion herausgerechnet
    - Mehr Schmutz: dp steigt schneller → t_pct größer → Restzeit kürzt sich korrekt
    - Kein harter Sprung: bei dp = dp_limit → t_pct = 100 → remaining = 0
2026-05-20 feat: flow-detection based cycle start with pause/resume support
    - New state machine: waiting_for_flow → cycle_active ↔ cycle_paused
    - Dual-condition start: Q > threshold AND dp > dp_clean×0.5, stable for
    configurable window (default 10s auto)
    - Auto-threshold from cycle samples (min operational Q × 0.4)
    - Pause on Q=0, resume on flow return; max 7d pause before abort
    - operation_mode (continuous/batch) with different pause tolerances
2026-05-21 fix: Prozessanalyse nach Lernphase funktioniert nicht mehr
    Wenn quick-learn aufgerufen wurde während awaiting_confirmation=True
    (dp-Limit gerade erreicht, Filterwechsel-Bestätigung ausstehend), schläft
    der Messzyklus-Thread danach dauerhaft – analysis_ready bleibt False.
    Ursache: api_simulation_quick_learn hat awaiting_confirmation nicht
    zurückgesetzt und waiting_for_flow nicht auf True gesetzt.
    Fixes:
2026-05-21 feat: Prozessanalyse mit dp-Steigung und Laufzeit-Anzeige
    Δp-Zeile in der Analyse:
    Statt absolutem dp (war bei dp-basierter Achse immer ~0 % Abweichung)
    wird jetzt die dp-Steigung (mbar/s) verglichen:
    Referenz-Steigung: Ableitung der Referenzkurve an der aktuellen
    dp-Position × (100 / ref_duration)
    Aktuelle Steigung: lineare Regression über letztes 30-s-Fenster
2026-05-21 fix: Referenzfenster rückwärts ausrichten — kein systematischer Versatz
    Ursache des Lags: _slope_windowed nutzte ein zentriertes Fenster
    (t_pct ± 15 s), die Regression nutzt ein rückwärts gerichtetes Fenster
    (letzte 30 s). Bei beschleunigender dp-Kurve ist die zentrierte Referenz
    stets höher als die rückwärtige Regression → systematischer Versatz auch
    bei identischem Prozess.
    Fix: Referenzfenster jetzt ebenfalls rückwärts (t_pct - 30s bis t_pct).
2026-05-21 fix: Reststandzeit startet aus Referenzdauer der Lernzyklen
    - prediction.py: seed() ist jetzt aktiv und setzt _last_remaining
    - app.py: _seed_predictor_from_profile() liest reference_duration_seconds
    aus dem validierten Profil und übergibt es an predictor.seed()
    - Wird an beiden Zyklusstarts aufgerufen (Simulation + Echtbetrieb)
    - Nur wenn Profil validiert ist; während der Lernphase kein Seeding
2026-05-21 fix: Messung blockiert solange Onboarding nicht abgeschlossen
    - Backend: /api/simulation/start gibt 403 zurück wenn onboarding_complete=false
    - Frontend: startPolling() erst nach erfolgreichem Onboarding-Check starten
    - Nach completeOnboarding() Polling sofort aktivieren (vor reload)
    - HETA-Code im Wizard: nur reines Zahlen-Eingabefeld, kein HETA- Prefix
2026-05-22 fix: checkOnboarding() gibt bei Netzwerkfehler false zurück
    Der catch-Block fiel bisher durch zu return true, sodass
    startPolling() bei einem temporären Serverfehler beim Seitenaufruf
    gestartet wurde – auch wenn das Onboarding noch nicht abgeschlossen
    war. Im Fehlerfall ist der Status unklar, daher false zurückgeben.
    https://claude.ai/code/session_019F7TYFr3YhasG8ewsCuTUG
2026-05-22 fix: PAUSE-Events als zeitgespannte Bereiche im Zyklus-Diagramm
    PAUSE_START und PAUSE_ENDE wurden als zwei separate Punktereignisse
    (ts_end=None) gespeichert – im Diagramm zwei Linien statt eines
    markierten Pausenbereichs.
    PAUSE_START öffnet jetzt ein Event mit category="pause";
    beim Fortsetzen schließt close_event(category="pause") das Event
    mit dem korrekten ts_end. Frontend rendert den Pausenzeitraum
2026-05-25 docs: Dokumentation für Zyklusfortschritt-Chart und Änderungsraten aktualisiert
    - README: Live-Ratendiagramm-Beschreibung und HETA-Prognose bei reduzierter Schmutzfracht ergänzt
    - Benutzerhandbuch: Abschnitt "Live-Diagramm (System-Tab)" neu geschrieben mit Tabelle der Änderungsraten-Kanäle
    - Softwarearchitektur: Glättungsalgorithmus-Abschnitt erweitert (BASIS vs. HETA_VALIDIERT), neuer Abschnitt "System-Tab: Live-Chart"
    https://claude.ai/code/session_019F7TYFr3YhasG8ewsCuTUG
2026-05-26 chore: .gitignore um .env und *.egg ergänzt
    https://claude.ai/code/session_019F7TYFr3YhasG8ewsCuTUG
2026-05-28 chore: ruff-Linting einrichten und alle Backend-Module bereinigt
    - pyproject.toml: ruff-Konfiguration (select E/W/F/I/UP/B/SIM, line-length 120)
    - .github/workflows/lint.yml: CI-Workflow – ruff check + ruff format auf push/PR
    - backend/*.py: ruff --fix angewendet (Import-Sortierung, ungenutzte Imports,
    UP-Upgrades, F841-Variablen); 63 Fehler automatisch behoben
    https://claude.ai/code/session_019F7TYFr3YhasG8ewsCuTUG
2026-05-29 ux: "Druckabfall bei sauberem Filterelement" verständlich umbenannt
    Label → "Referenz-Differenzdruck (frischer Filter)"
    Hilfetext → "Wird automatisch beim ersten Einschalten eines neuen Filters gemessen."
    https://claude.ai/code/session_019F7TYFr3YhasG8ewsCuTUG
2026-06-08 fix: Sensor-Vorprüfung vor Durchfluss-Check im Hardware-Modus
    Ursache: Nach Wechsel Simulation→Hardware wurde waiting_for_flow=True
    gesetzt. Ohne angeschlossene Sensoren war sensor_error=True dauerhaft,
    flow_ok wurde nie True → stille Endlosschleife ohne erkennbaren Fehler.
    Lösung: Sensor-Vorprüfung am Beginn des waiting_for_flow-Blocks.
    Sind nicht alle Sensoren verfügbar (sensor_error=True, Hardware-Modus),
    wird sofort STATUS_FEHLER gesetzt und flow_check_sensor_error=True im
